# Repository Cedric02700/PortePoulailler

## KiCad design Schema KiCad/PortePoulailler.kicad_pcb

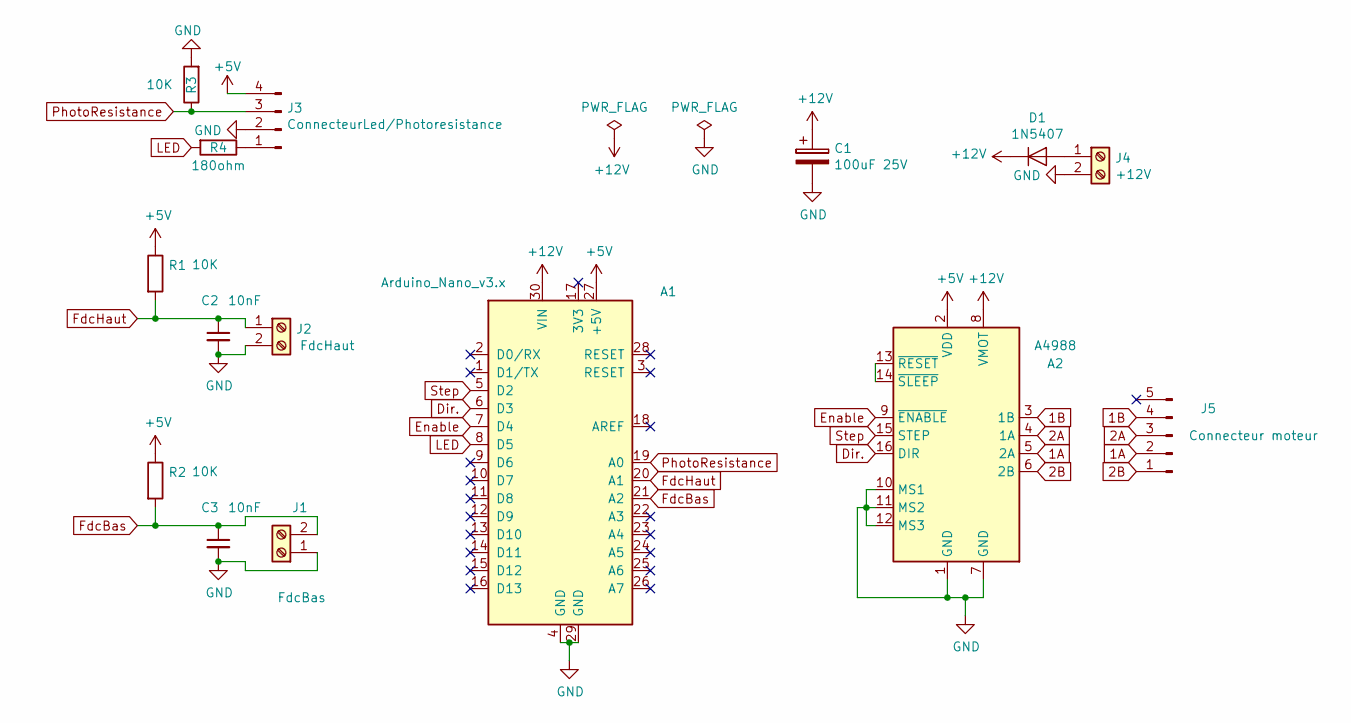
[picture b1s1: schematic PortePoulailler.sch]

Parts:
A1: Arduino_Nano_v3.x; Arduino_Nano
A2: A4988; Pololu_Breakout-16_15.2x20.3mm
C1: 100uF 25V; CP_Radial_D6.3mm_P2.50mm
C2, C3: 10nF; C_Disc_D5.0mm_W2.5mm_P2.50mm
D1: 1N5407; D_DO-201AD_P5.08mm_Vertical_AnodeUp
J1: FdcBas; TerminalBlock_Altech_AK300-2_P5.00mm
J2: FdcHaut; TerminalBlock_Altech_AK300-2_P5.00mm
J3: ConnecteurLed/Photoresistance; JST_XH_B04B-XH-A_1x04_P2.50mm_Vertical
J4: +12V; TerminalBlock_Altech_AK300-2_P5.00mm
J5: Connecteur moteur; JST_XH_B05B-XH-A_1x05_P2.50mm_Vertical
R1, R2, R3: 10K; R_Axial_DIN0414_L11.9mm_D4.5mm_P15.24mm_Horizontal
R4: 180ohm; R_Axial_DIN0414_L11.9mm_D4.5mm_P15.24mm_Horizontal

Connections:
1A: A2.5 (2A), J5.2
1B: A2.3 (1B), J5.4
2A: A2.4 (1A), J5.3
2B: A2.6 (2B), J5.1
+5V: A1.27 (+5V), A2.2 (VDD), J3.4, R1.1, R2.1
+12V: A1.30 (VIN), A2.8 (VMOT), C1.1, D1.1 (K)
Dir.: A1.6 (D3), A2.16 (DIR)
Enable: A1.7 (D4), A2.9 (~ENABLE)
FdcBas: A1.21 (A2), C3.1, J1.2, R2.2
FdcHaut: A1.20 (A1), C2.1, J2.1, R1.2
GND: A1.4 (GND), A1.29 (GND), A2.1 (GND), A2.7 (GND), A2.10 (MS1), A2.11 (MS2), A2.12 (MS3), C1.2, C2.2, C3.2, J1.1, J2.2, J3.2, J4.2, R3.2
LED: A1.8 (D5), R4.2
unnamed: A2.13 (~RESET), A2.14 (~SLEEP)
unnamed: D1.2 (A), J4.1
unnamed: J3.1, R4.1
PhotoResistance: A1.19 (A0), J3.3, R3.1
Step: A1.5 (D2), A2.15 (STEP)

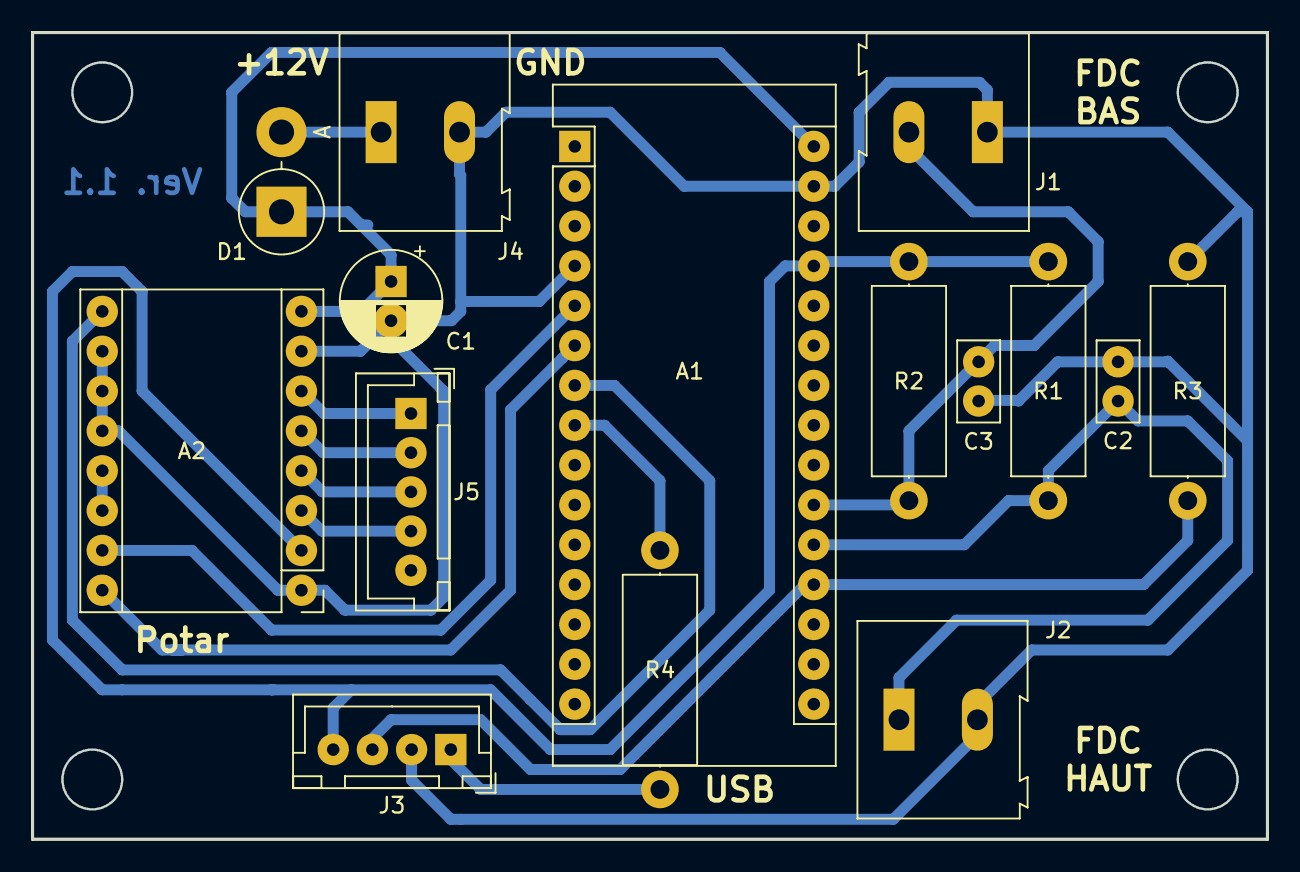
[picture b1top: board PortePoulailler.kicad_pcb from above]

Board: 2 copper layers, 78.7 x 51.4 mm, 15 parts (0 on the bottom side), 17 nets.

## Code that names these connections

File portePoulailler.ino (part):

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//unsigned long delaiEntreOuverte = 10000;       //delai ou la porte reste entre ouverte en ms

//********** Declaration des constantes **********************************************************************
const int photoResistance = A0;      //Photo resistance connecté sur Pin A0 de l'arduino
const int Step = 2;                  //Pin step du A4988 connecté sur Pin 2 de l'arduino
const int Dir = 3;                   //Pin dir du A4988 connecté sur Pin 3 de l'arduino
const int Enable = 4;                //Pin step du A4988 connecté sur Pin 4 de l'arduino
const int LED = 5;                   //LED connecté sur Pin 5 de l'arduino
const int FdcHaut = A1;              //Fin de course haut connecté sur Pin A1 de l'arduino
const int FdcBas = A2;               //Fin de course bas connecté sur Pin A2 de l'arduino

//********** Declaration des variables pour l'ouverture/fermeture de la porte ********************************
int etatPorte;                               //0: ouverte; 1: fermee; 2: entre ouverte   
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  pinMode(Step, OUTPUT);
  pinMode(Dir, OUTPUT);
  pinMode(Enable, OUTPUT);
  pinMode(FdcHaut, INPUT);
  pinMode(FdcBas, INPUT);
  etatFdcHaut = digitalRead(FdcHaut);
  digitalWrite(Dir, HIGH);                    //moteur sens monter
  digitalWrite(Enable, LOW);                  //Active le moteur
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
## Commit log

2019-03-24 Ajout de quelque fonction. Travail en cours de progression.
2019-03-26 Ajout de quelques fonctions plus correction de bug.
2019-03-26 Correction de bug
2019-03-29 Avancee du jour.
2019-04-17 Ajout schema Kicad
2019-12-07 Ca avance
2019-12-07 Correction Bug calibration().
2019-12-15 Avancées sur le code portePoulailler.ino et ajout du code EEprom.ino
2019-12-31 Code complet à nettoyer
2020-03-29 Version fonctionnelle
2020-03-29 Mise a jour et début de rédaction de la notice
